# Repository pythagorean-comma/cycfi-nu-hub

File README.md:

# Cycfi Nu Hub

A 6-channel hub board for wiring six individual **Cycfi Nu v2 capsules** into a v2.6
**Cycfi Internal Breakout** on channels 1–6.

Built against Cycfi's published Eagle sources at
<https://github.com/cycfi/nu>

50 × 35 mm on the **Internal Breakout's own outline and M2 hole pattern**, two
layers, and **no components** — thirteen connectors, a grounding pad and some
copper. The capsules already decouple themselves, so there is nothing left for
this board to do but join things up correctly.

The outline is measured from Cycfi's Eagle files, which are **v2.5**; no
dimension has ever been published for the v2.6 this hub is wired for. That
costs nothing electrically and is an open assumption mechanically — see
[`docs/DESIGN.md`](docs/DESIGN.md).

## Everything is generated

`design.py` is the single source of truth for the circuit. `gen_sch.py` draws
the schematic from it, `gen_pcb.py` places and routes the board from it, and
`verify.py` reads KiCad's own netlist back and compares it net by net.

```bash
./build.sh
```

That regenerates schematic *and* board, runs ERC, checks both against
`design.py`, runs DRC, and writes `fab/cycfi-nu-hub-pcbway.zip`, but **only
when DRC is clean**, so a board with known faults cannot reach a fab by
accident.

## Two boards

There is a second variant that **deletes the Internal Breakout entirely** and
drives the instrument's 19-pin output jack itself — 35 × 24.5 mm, half the
area, one polyfuse and one capacitor:

```bash
./build.sh direct
```

The capsule end of both boards is identical; only what the six channels arrive
at differs. The generators are shared and `design.VARIANT` picks between them.

**Order the default one.** The direct variant assumes the v2.6 breakout
presents its jack on the same two 2×5 headers v2.5 does, and nobody has
checked that against hardware. [`docs/DESIGN.md`](docs/DESIGN.md) has the
evidence, the two components' justification, and the one safety property that
regresses.

> **Anything changed in the KiCad GUI is destroyed by the next build.** Use the
> editor to inspect, measure and try things out; changes that should survive
> belong in the generator.

`design.py` also holds the two pin maps transcribed from Cycfi's schematics
and asserts the board against them at import, so a hub wired to the wrong
channels fails to load rather than fails on the bench.

## Requirements

**KiCad 10.x.** Install with `brew install --cask kicad`, or from
<https://www.kicad.org/download/>. The file formats written are version
specific: KiCad 9 will not open the generated schematic.

**No Python packages.** There is no virtual environment and no
`requirements.txt`, because there is nothing to install: the generators are
pure standard library. The one exception is `pcbnew`, which ships inside KiCad,
so `build.sh` runs `gen_pcb.py` under KiCad's own bundled interpreter and
everything else under `python3`. Set `PYTHON` to override which one.

`kicad.py` finds the installation. It checks `$KICAD_APP`, then
`/Applications/KiCad/KiCad.app`, then `~/Applications/KiCad/KiCad.app`, then
`kicad-cli` on `PATH`. If yours lives somewhere else:

```bash
export KICAD_APP=/path/to/KiCad.app
```

Run `python3 kicad.py` to see what it found.

## Where to read next

| | |
| --- | --- |
| [`docs/DESIGN.md`](docs/DESIGN.md) | What the board does and why, what must not be got wrong when wiring it, how it came out, and what is still open. **Start here.** |
| [`docs/CABLES.md`](docs/CABLES.md) | How to make the thirteen cables: parts, suppliers, position-by-position tables, and the continuity checks to run before anything is powered. |
| [`fab/ORDER.md`](fab/ORDER.md) | How to order it, including the four requirements that are invisible in the gerbers, and what to buy alongside it. It lives beside the gerbers rather than in `docs/` because `build.sh` copies it into the fabrication zip and `verify.py` checks the board against its figures. |
| [`docs/cycfi-sources.md`](docs/cycfi-sources.md) | What Cycfi's own files say, at a recorded commit, and how to re-extract it. Records, not specifications — where they and `docs/DESIGN.md` differ, `docs/DESIGN.md` is right. |

## Status

Generated, checked and clean: ERC 0, DRC 0 — **warnings included, not just
errors** — and the schematic matches `design.py` across 8 nets and 39 pin
connections. A fabrication package is written.

**Nothing has been made yet.** No board has been fabricated, no cable crimped
and nothing measured, so every claim in this repository comes from Cycfi's
sources and from the generators — not from a bench.

Three things to settle before ordering, all in the last section of
[`docs/DESIGN.md`](docs/DESIGN.md): Cycfi publish sources for breakout **v2.5** and this
targets **v2.6**, which is three continuity readings on J3 to confirm; the
breakout's `PWR SELECT` jumper decides what voltage six capsules will see; and
the outline copied here is **v2.5's**, because no dimension for v2.6 has ever
been published. Measuring a v2.6 board — width, height, hole diameter, hole
centres — is what closes the last one, and `design.MOUNTING_PATTERN` is the
single block that would change.

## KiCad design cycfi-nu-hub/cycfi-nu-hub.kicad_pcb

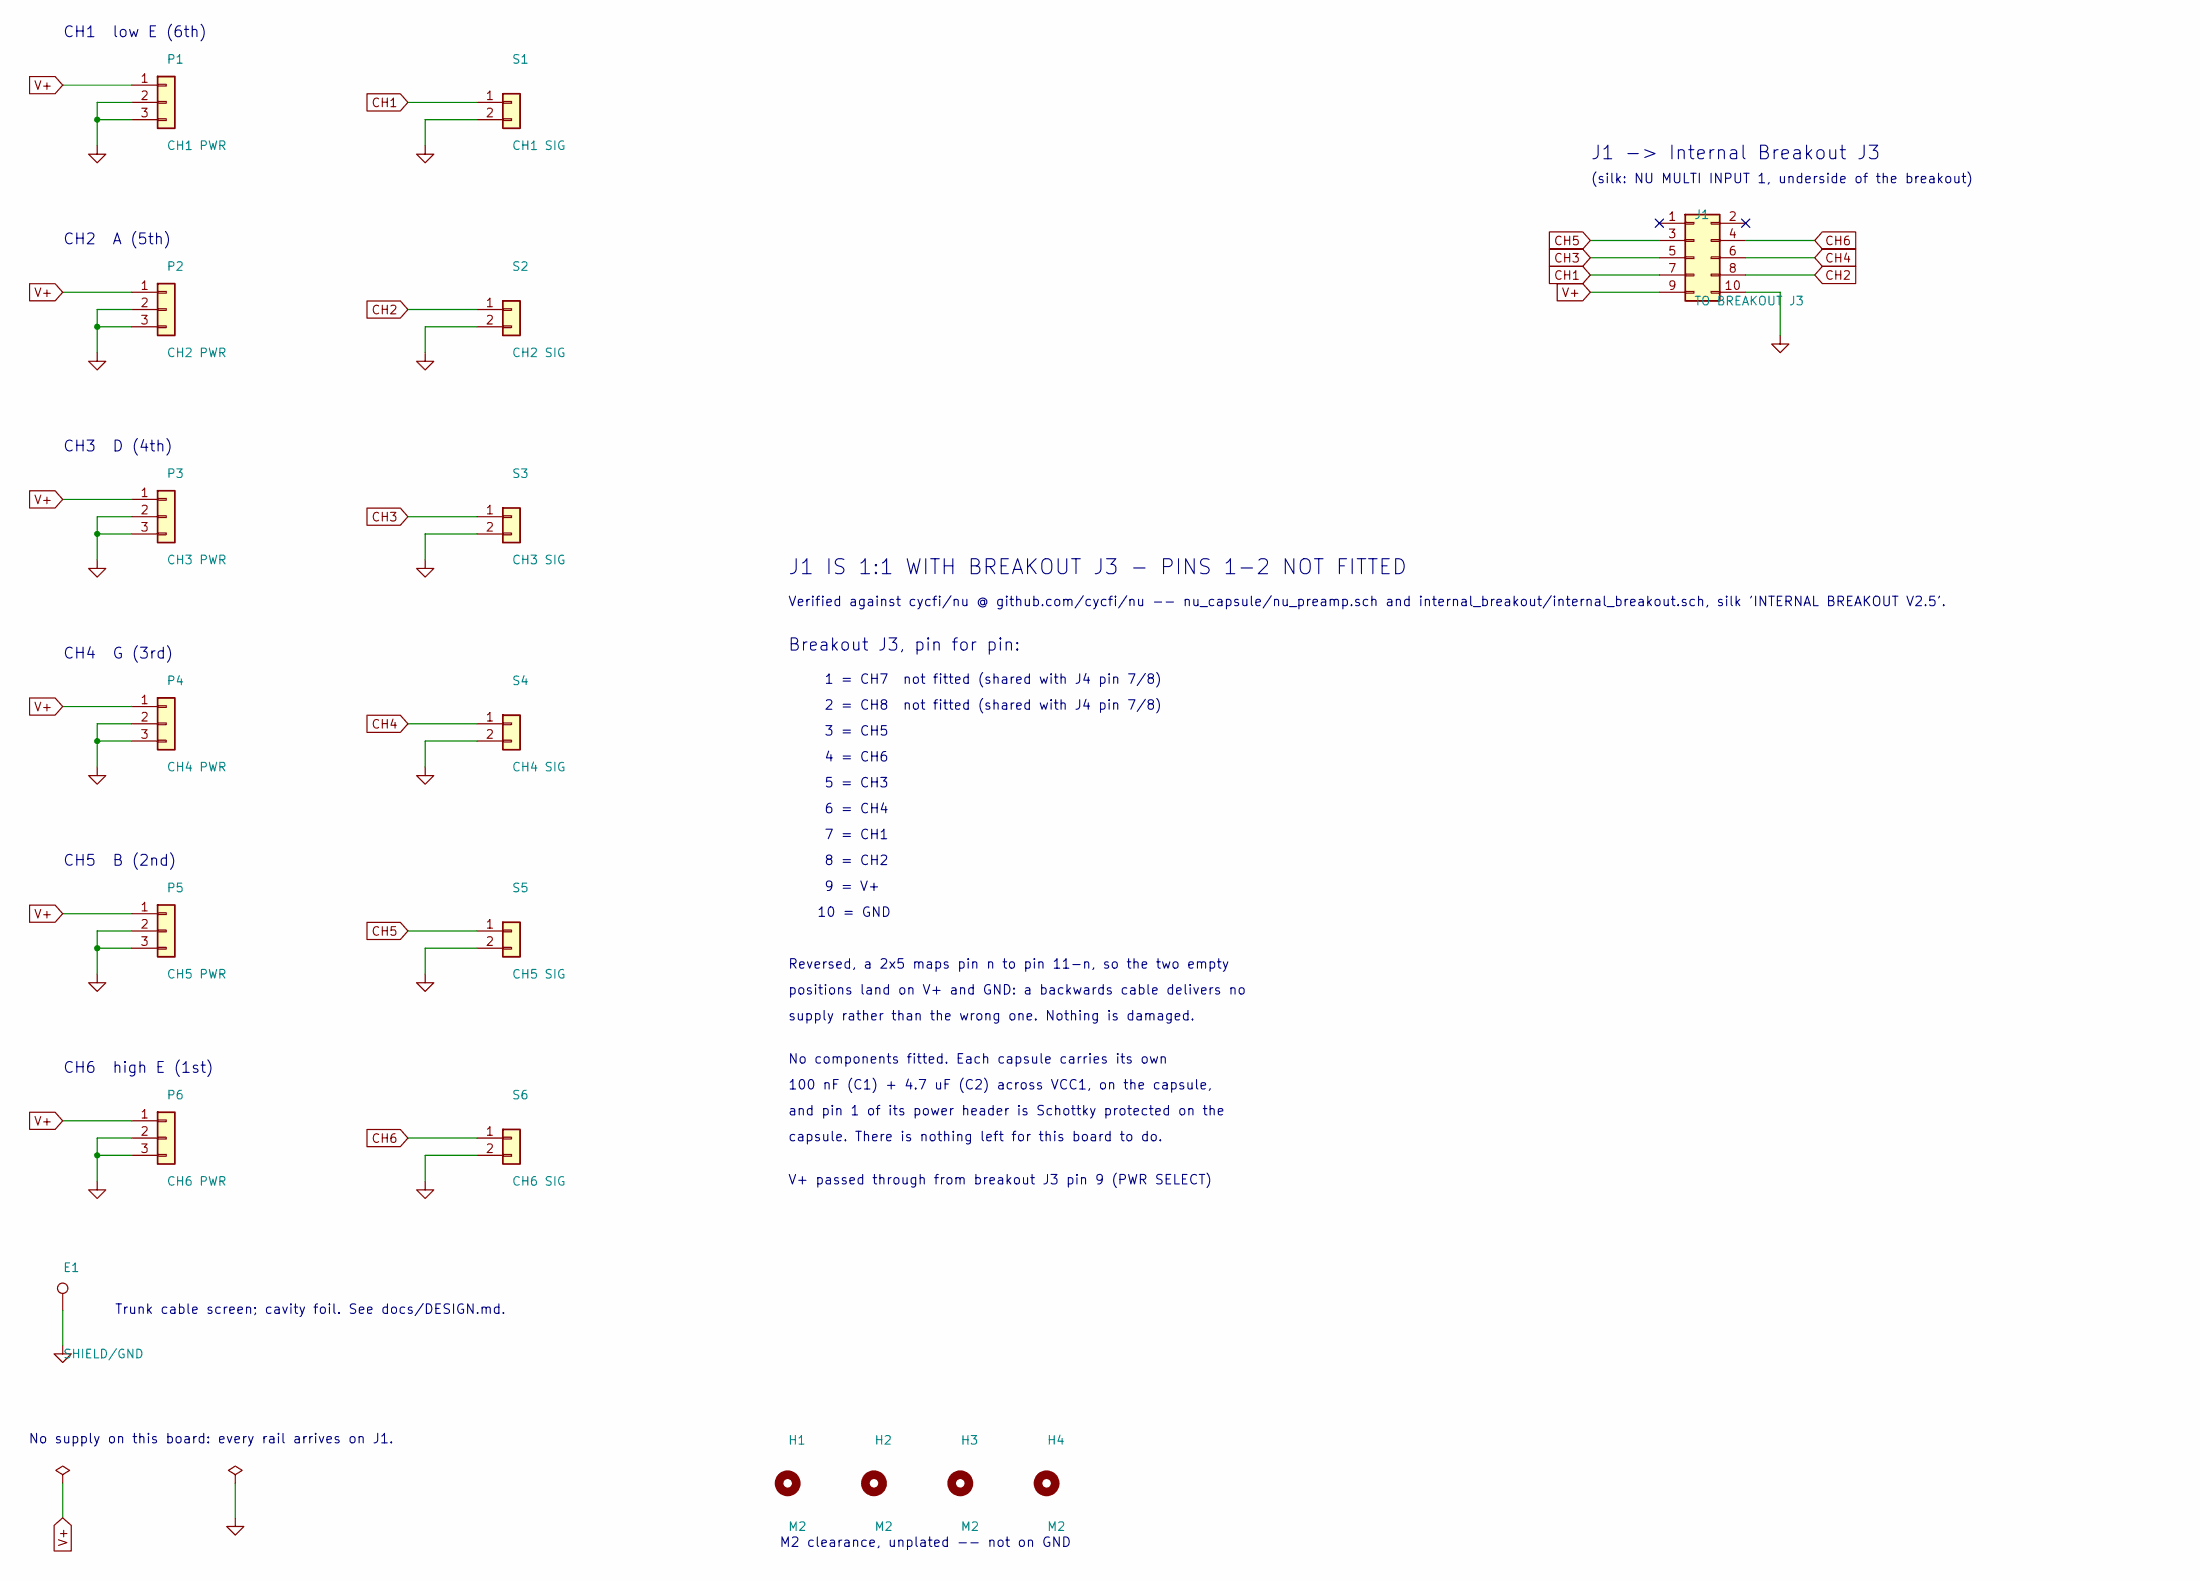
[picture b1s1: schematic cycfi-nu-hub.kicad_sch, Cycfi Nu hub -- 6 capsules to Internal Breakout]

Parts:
E1: SHIELD/GND; TestPoint_THTPad_2.0x2.0mm_Drill1.0mm
H1, H2, H3, H4: M2; MountingHole_2.2mm_M2
J1: TO BREAKOUT J3; PinHeader_2x05_P2.00mm_Vertical
P1: CH1 PWR; PinHeader_1x03_P2.00mm_Vertical
P2: CH2 PWR; PinHeader_1x03_P2.00mm_Vertical
P3: CH3 PWR; PinHeader_1x03_P2.00mm_Vertical
P4: CH4 PWR; PinHeader_1x03_P2.00mm_Vertical
P5: CH5 PWR; PinHeader_1x03_P2.00mm_Vertical
P6: CH6 PWR; PinHeader_1x03_P2.00mm_Vertical
S1: CH1 SIG; PinHeader_1x02_P2.00mm_Vertical
S2: CH2 SIG; PinHeader_1x02_P2.00mm_Vertical
S3: CH3 SIG; PinHeader_1x02_P2.00mm_Vertical
S4: CH4 SIG; PinHeader_1x02_P2.00mm_Vertical
S5: CH5 SIG; PinHeader_1x02_P2.00mm_Vertical
S6: CH6 SIG; PinHeader_1x02_P2.00mm_Vertical

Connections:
CH1: J1.7, S1.1
CH2: J1.8, S2.1
CH3: J1.5, S3.1
CH4: J1.6, S4.1
CH5: J1.3, S5.1
CH6: J1.4, S6.1
GND: E1.1, J1.10, P1.2, P1.3, P2.2, P2.3, P3.2, P3.3, P4.2, P4.3, P5.2, P5.3, P6.2, P6.3, S1.2, S2.2, S3.2, S4.2, S5.2, S6.2
V+: J1.9, P1.1, P2.1, P3.1, P4.1, P5.1, P6.1

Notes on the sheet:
CH1 low E (6th)
CH2 A (5th)
CH3 D (4th)
CH4 G (3rd)
CH5 B (2nd)
CH6 high E (1st)
J1 -> Internal Breakout J3
(silk: NU MULTI INPUT 1, underside of the breakout)
Trunk cable screen; cavity foil. See docs/DESIGN.md.
M2 clearance, unplated -- not on GND
No supply on this board: every rail arrives on J1.
J1 IS 1:1 WITH BREAKOUT J3 - PINS 1-2 NOT FITTED
Verified against cycfi/nu @ github.com/cycfi/nu -- nu_capsule/nu_preamp.sch and internal_breakout/internal_breakout.sch, silk 'INTERNAL BREAKOUT V2.5'.
Breakout J3, pin for pin:
1 = CH7 not fitted (shared with J4 pin 7/8)
2 = CH8 not fitted (shared with J4 pin 7/8)
3 = CH5
4 = CH6
5 = CH3
6 = CH4
7 = CH1
8 = CH2
9 = V+
10 = GND
Reversed, a 2x5 maps pin n to pin 11-n, so the two empty
positions land on V+ and GND: a backwards cable delivers no
supply rather than the wrong one. Nothing is damaged.
No components fitted. Each capsule carries its own
100 nF (C1) + 4.7 uF (C2) across VCC1, on the capsule,
and pin 1 of its power header is Schottky protected on the
capsule. There is nothing left for this board to do.
V+ passed through from breakout J3 pin 9 (PWR SELECT)

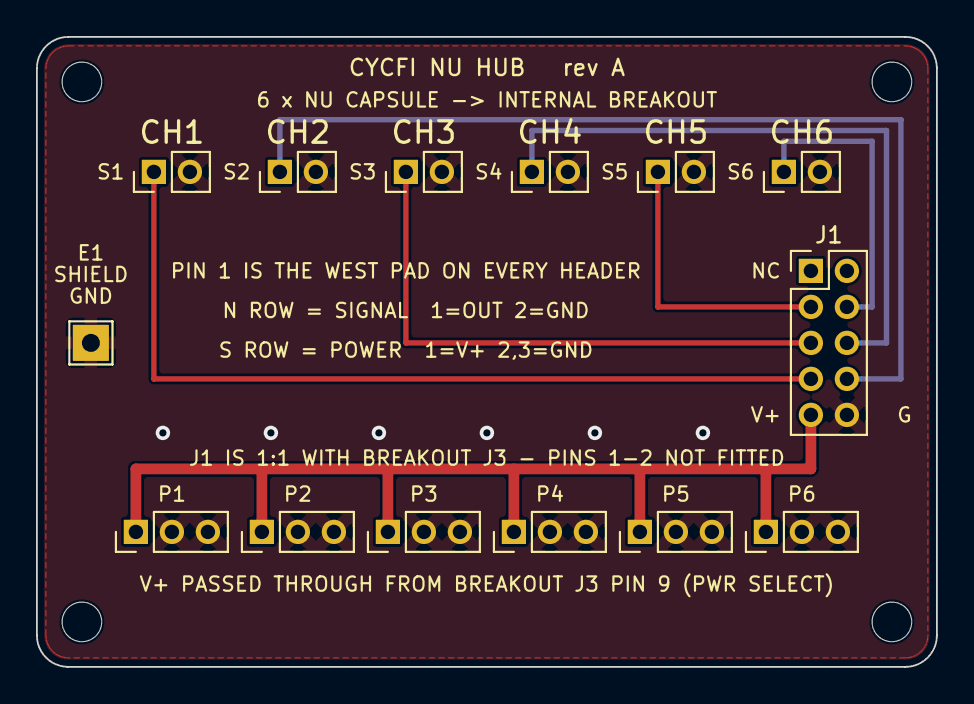
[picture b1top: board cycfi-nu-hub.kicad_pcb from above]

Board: 2 copper layers, 50.0 x 35.0 mm, 18 parts (0 on the bottom side), 8 nets.

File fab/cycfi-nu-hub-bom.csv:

"Reference","Value","Footprint","QUANTITY","Description"
"E1","SHIELD/GND","TestPoint:TestPoint_THTPad_2.0x2.0mm_Drill1.0mm","1","Solder pad to GND: trunk cable screen, cavity foil, optionally bridge earth"
"H1-H4","M2","MountingHole:MountingHole_2.2mm_M2","4","M2 clearance hole, unplated"
"J1","TO BREAKOUT J3","Connector_PinHeader_2.00mm:PinHeader_2x05_P2.00mm_Vertical","1","2x5 2.00mm to Internal Breakout J3 (NU MULTI INPUT 1); pins 1-2 not fitted"
"P1","CH1 PWR","Connector_PinHeader_2.00mm:PinHeader_1x03_P2.00mm_Vertical","1","Capsule 1, low E (6th) -- power, to capsule H2: 1=V+, 2=GND, 3=GND"
"P2","CH2 PWR","Connector_PinHeader_2.00mm:PinHeader_1x03_P2.00mm_Vertical","1","Capsule 2, A (5th) -- power, to capsule H2: 1=V+, 2=GND, 3=GND"
"P3","CH3 PWR","Connector_PinHeader_2.00mm:PinHeader_1x03_P2.00mm_Vertical","1","Capsule 3, D (4th) -- power, to capsule H2: 1=V+, 2=GND, 3=GND"
"P4","CH4 PWR","Connector_PinHeader_2.00mm:PinHeader_1x03_P2.00mm_Vertical","1","Capsule 4, G (3rd) -- power, to capsule H2: 1=V+, 2=GND, 3=GND"
"P5","CH5 PWR","Connector_PinHeader_2.00mm:PinHeader_1x03_P2.00mm_Vertical","1","Capsule 5, B (2nd) -- power, to capsule H2: 1=V+, 2=GND, 3=GND"
"P6","CH6 PWR","Connector_PinHeader_2.00mm:PinHeader_1x03_P2.00mm_Vertical","1","Capsule 6, high E (1st) -- power, to capsule H2: 1=V+, 2=GND, 3=GND"
"S1","CH1 SIG","Connector_PinHeader_2.00mm:PinHeader_1x02_P2.00mm_Vertical","1","Capsule 1, low E (6th) -- signal, to capsule H1: 1=OUT, 2=GND"
"S2","CH2 SIG","Connector_PinHeader_2.00mm:PinHeader_1x02_P2.00mm_Vertical","1","Capsule 2, A (5th) -- signal, to capsule H1: 1=OUT, 2=GND"
"S3","CH3 SIG","Connector_PinHeader_2.00mm:PinHeader_1x02_P2.00mm_Vertical","1","Capsule 3, D (4th) -- signal, to capsule H1: 1=OUT, 2=GND"
"S4","CH4 SIG","Connector_PinHeader_2.00mm:PinHeader_1x02_P2.00mm_Vertical","1","Capsule 4, G (3rd) -- signal, to capsule H1: 1=OUT, 2=GND"
"S5","CH5 SIG","Connector_PinHeader_2.00mm:PinHeader_1x02_P2.00mm_Vertical","1","Capsule 5, B (2nd) -- signal, to capsule H1: 1=OUT, 2=GND"
"S6","CH6 SIG","Connector_PinHeader_2.00mm:PinHeader_1x02_P2.00mm_Vertical","1","Capsule 6, high E (1st) -- signal, to capsule H1: 1=OUT, 2=GND"

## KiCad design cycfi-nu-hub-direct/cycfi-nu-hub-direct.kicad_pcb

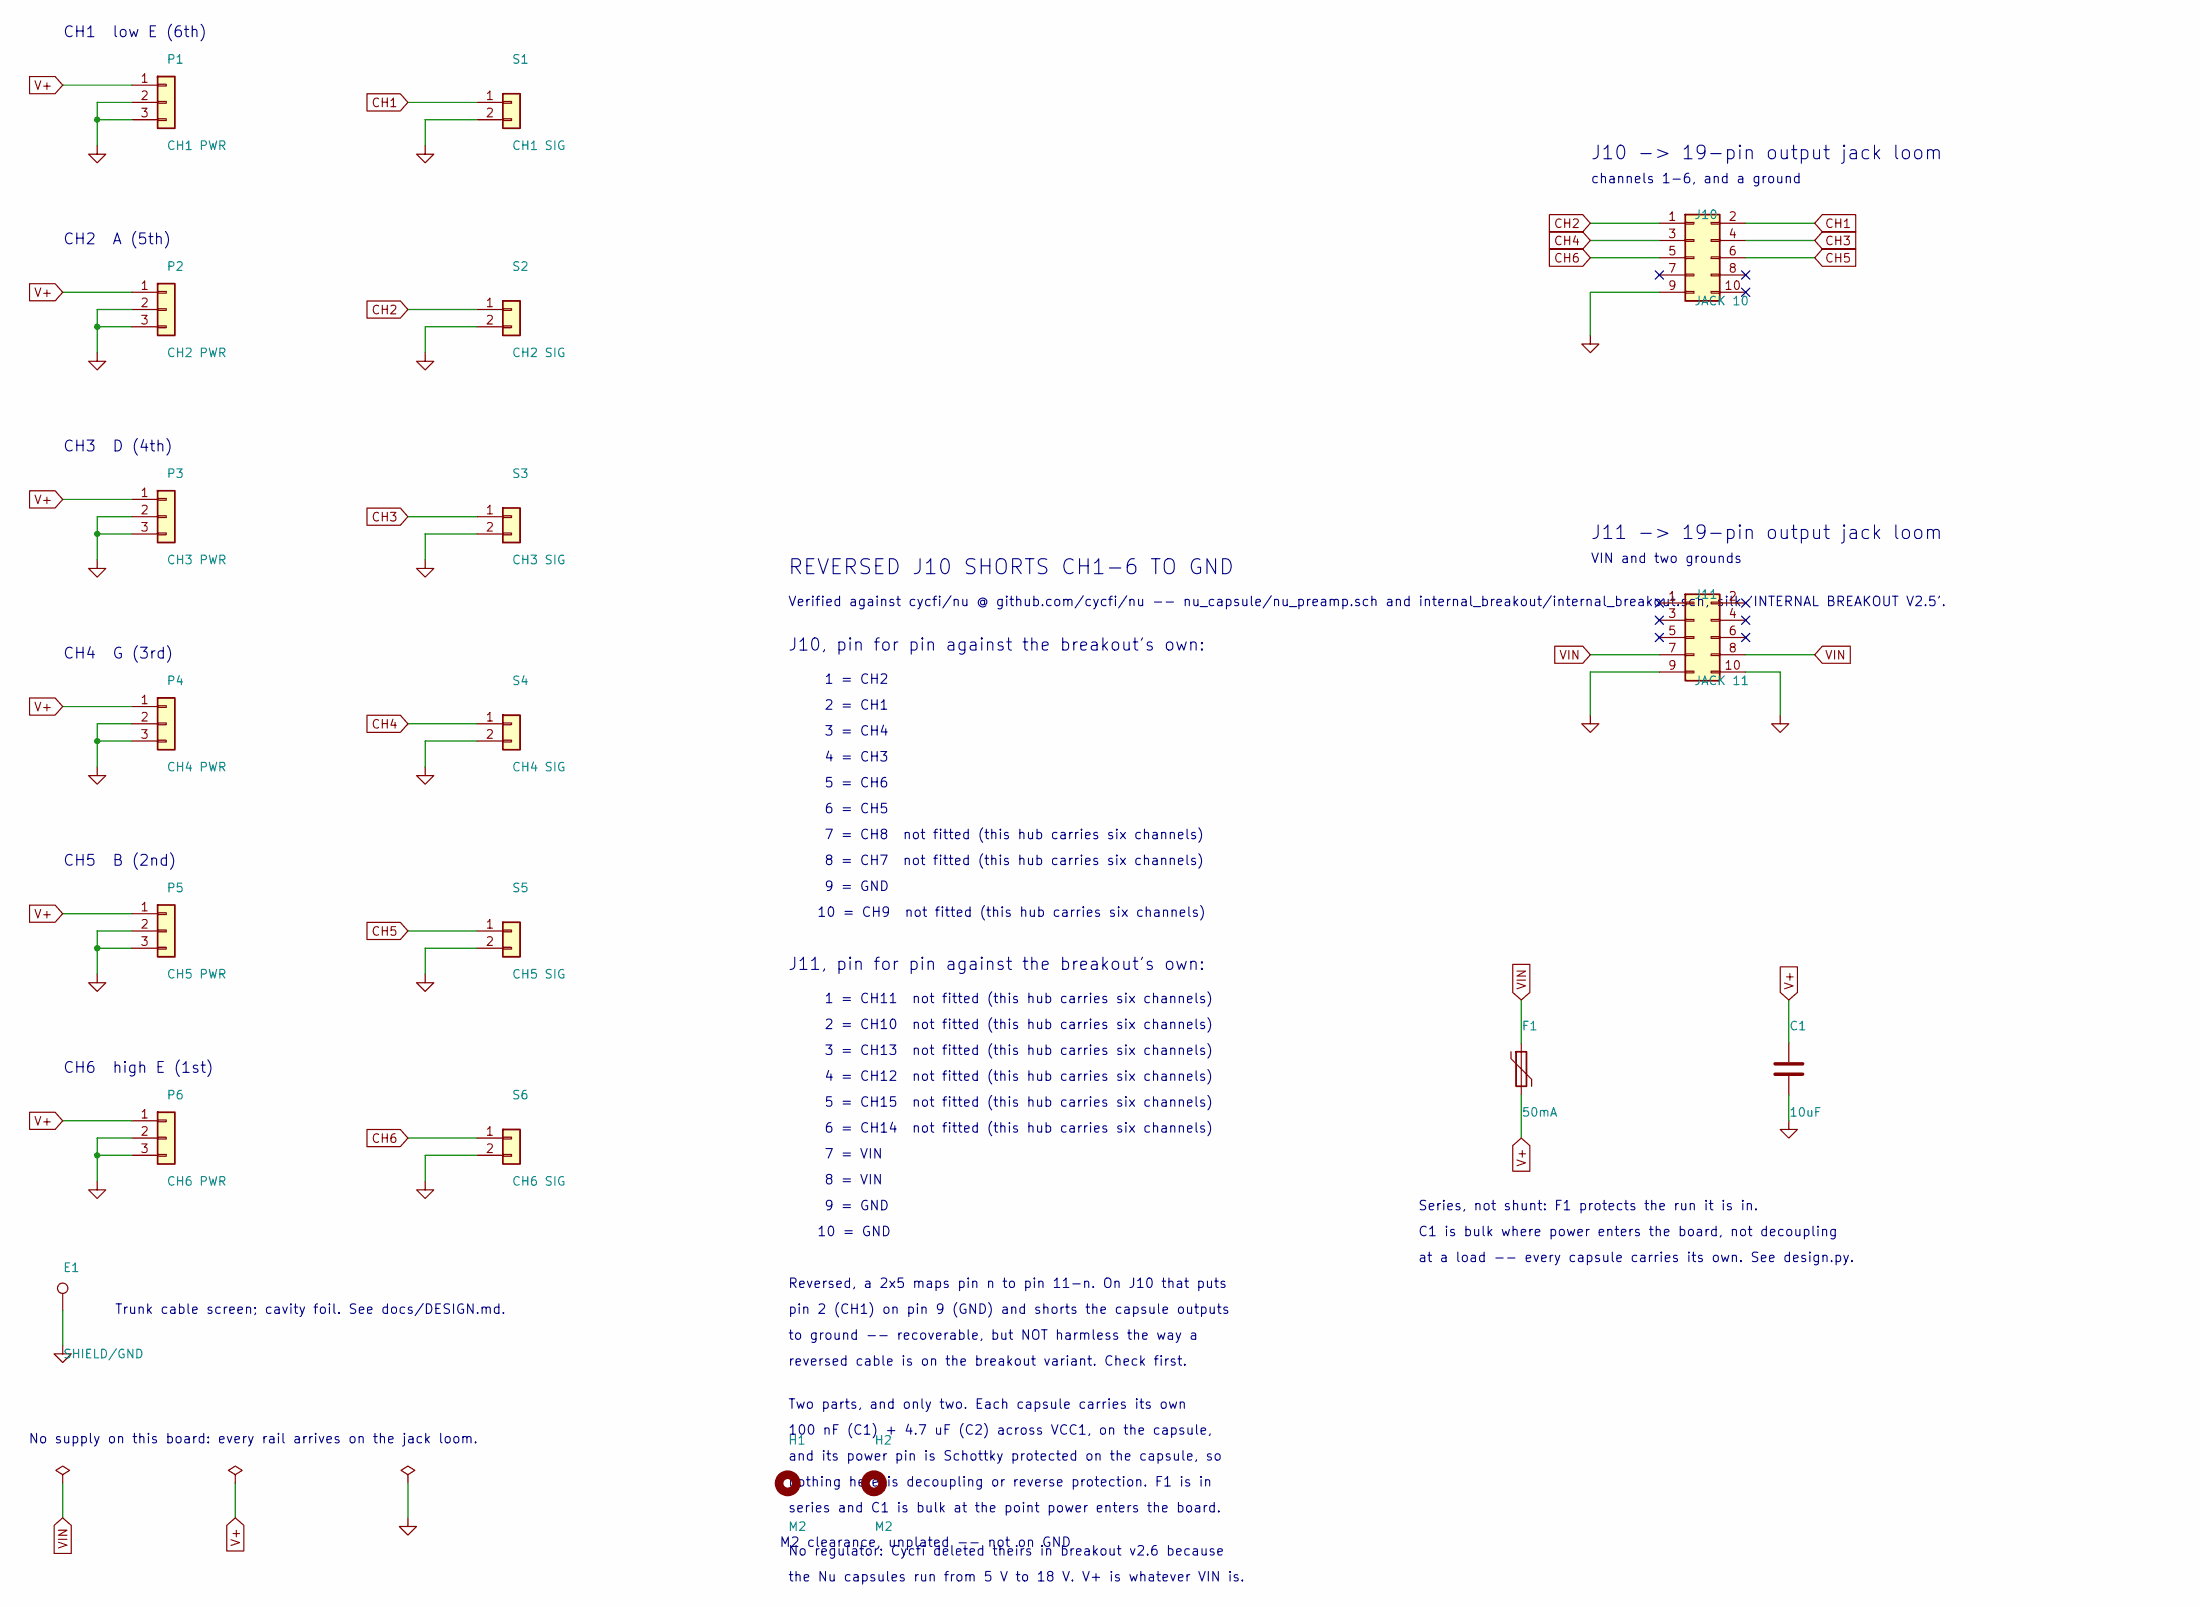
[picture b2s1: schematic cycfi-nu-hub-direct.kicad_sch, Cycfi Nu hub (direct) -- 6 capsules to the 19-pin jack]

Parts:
C1: 10uF; C_0805_2012Metric
E1: SHIELD/GND; TestPoint_THTPad_2.0x2.0mm_Drill1.0mm
F1: 50mA; Fuse_0805_2012Metric
H1, H2: M2; MountingHole_2.2mm_M2
J10: JACK 10; PinHeader_2x05_P2.00mm_Vertical
J11: JACK 11; PinHeader_2x05_P2.00mm_Vertical
P1: CH1 PWR; PinHeader_1x03_P2.00mm_Vertical
P2: CH2 PWR; PinHeader_1x03_P2.00mm_Vertical
P3: CH3 PWR; PinHeader_1x03_P2.00mm_Vertical
P4: CH4 PWR; PinHeader_1x03_P2.00mm_Vertical
P5: CH5 PWR; PinHeader_1x03_P2.00mm_Vertical
P6: CH6 PWR; PinHeader_1x03_P2.00mm_Vertical
S1: CH1 SIG; PinHeader_1x02_P2.00mm_Vertical
S2: CH2 SIG; PinHeader_1x02_P2.00mm_Vertical
S3: CH3 SIG; PinHeader_1x02_P2.00mm_Vertical
S4: CH4 SIG; PinHeader_1x02_P2.00mm_Vertical
S5: CH5 SIG; PinHeader_1x02_P2.00mm_Vertical
S6: CH6 SIG; PinHeader_1x02_P2.00mm_Vertical

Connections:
CH1: J10.2, S1.1
CH2: J10.1, S2.1
CH3: J10.4, S3.1
CH4: J10.3, S4.1
CH5: J10.6, S5.1
CH6: J10.5, S6.1
GND: C1.2, E1.1, J10.9, J11.9, J11.10, P1.2, P1.3, P2.2, P2.3, P3.2, P3.3, P4.2, P4.3, P5.2, P5.3, P6.2, P6.3, S1.2, S2.2, S3.2, S4.2, S5.2, S6.2
V+: C1.1, F1.2, P1.1, P2.1, P3.1, P4.1, P5.1, P6.1
VIN: F1.1, J11.7, J11.8

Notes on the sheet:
CH1 low E (6th)
CH2 A (5th)
CH3 D (4th)
CH4 G (3rd)
CH5 B (2nd)
CH6 high E (1st)
J10 -> 19-pin output jack loom
channels 1-6, and a ground
J11 -> 19-pin output jack loom
VIN and two grounds
Series, not shunt: F1 protects the run it is in.
C1 is bulk where power enters the board, not decoupling
at a load -- every capsule carries its own. See design.py.
Trunk cable screen; cavity foil. See docs/DESIGN.md.
M2 clearance, unplated -- not on GND
No supply on this board: every rail arrives on the jack loom.
REVERSED J10 SHORTS CH1-6 TO GND
Verified against cycfi/nu @ github.com/cycfi/nu -- nu_capsule/nu_preamp.sch and internal_breakout/internal_breakout.sch, silk 'INTERNAL BREAKOUT V2.5'.
J10, pin for pin against the breakout's own:
1 = CH2
2 = CH1
3 = CH4
4 = CH3
5 = CH6
6 = CH5
7 = CH8 not fitted (this hub carries six channels)
8 = CH7 not fitted (this hub carries six channels)
9 = GND
10 = CH9 not fitted (this hub carries six channels)
J11, pin for pin against the breakout's own:
1 = CH11 not fitted (this hub carries six channels)
2 = CH10 not fitted (this hub carries six channels)
3 = CH13 not fitted (this hub carries six channels)
4 = CH12 not fitted (this hub carries six channels)
5 = CH15 not fitted (this hub carries six channels)
6 = CH14 not fitted (this hub carries six channels)
7 = VIN
8 = VIN
10 = GND
Reversed, a 2x5 maps pin n to pin 11-n. On J10 that puts

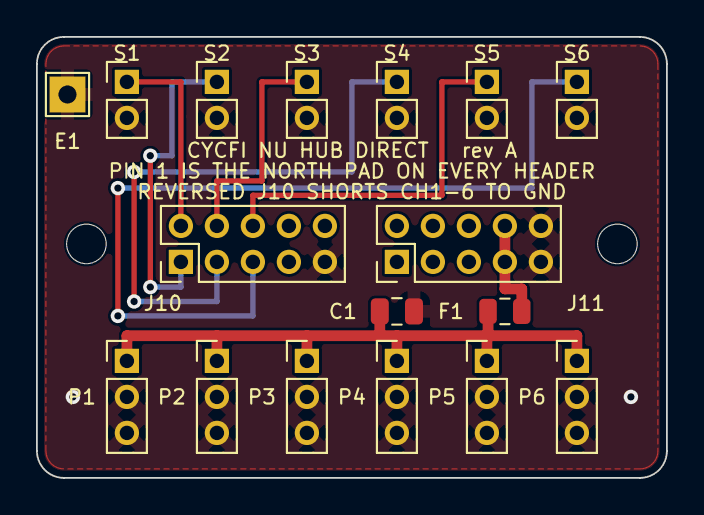
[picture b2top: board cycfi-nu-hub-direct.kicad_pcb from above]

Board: 2 copper layers, 35.0 x 24.5 mm, 19 parts (0 on the bottom side), 9 nets.

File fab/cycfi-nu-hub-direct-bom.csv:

"Reference","Value","Footprint","QUANTITY","Description"
"C1","10uF","Capacitor_SMD:C_0805_2012Metric","1","Bulk across V+ at the point power enters the board; not decoupling -- see NO_COMPONENTS"
"E1","SHIELD/GND","TestPoint:TestPoint_THTPad_2.0x2.0mm_Drill1.0mm","1","Solder pad to GND: trunk cable screen, cavity foil, optionally bridge earth"
"F1","50mA","Fuse:Fuse_0805_2012Metric","1","Polyfuse, 50 mA hold -- series protection for the six capsule supplies"
"H1,H2","M2","MountingHole:MountingHole_2.2mm_M2","2","M2 clearance hole, unplated"
"J10","JACK 10","Connector_PinHeader_2.00mm:PinHeader_2x05_P2.00mm_Vertical","1","2x5 2.00mm to the 19-pin output jack loom -- channels 1-6 and a ground; wired one-to-one with the breakout's J10"
"J11","JACK 11","Connector_PinHeader_2.00mm:PinHeader_2x05_P2.00mm_Vertical","1","2x5 2.00mm to the 19-pin output jack loom -- VIN and two grounds; wired one-to-one with the breakout's J11"
"P1","CH1 PWR","Connector_PinHeader_2.00mm:PinHeader_1x03_P2.00mm_Vertical","1","Capsule 1, low E (6th) -- power, to capsule H2: 1=V+, 2=GND, 3=GND"
"P2","CH2 PWR","Connector_PinHeader_2.00mm:PinHeader_1x03_P2.00mm_Vertical","1","Capsule 2, A (5th) -- power, to capsule H2: 1=V+, 2=GND, 3=GND"
"P3","CH3 PWR","Connector_PinHeader_2.00mm:PinHeader_1x03_P2.00mm_Vertical","1","Capsule 3, D (4th) -- power, to capsule H2: 1=V+, 2=GND, 3=GND"
"P4","CH4 PWR","Connector_PinHeader_2.00mm:PinHeader_1x03_P2.00mm_Vertical","1","Capsule 4, G (3rd) -- power, to capsule H2: 1=V+, 2=GND, 3=GND"
"P5","CH5 PWR","Connector_PinHeader_2.00mm:PinHeader_1x03_P2.00mm_Vertical","1","Capsule 5, B (2nd) -- power, to capsule H2: 1=V+, 2=GND, 3=GND"
"P6","CH6 PWR","Connector_PinHeader_2.00mm:PinHeader_1x03_P2.00mm_Vertical","1","Capsule 6, high E (1st) -- power, to capsule H2: 1=V+, 2=GND, 3=GND"
"S1","CH1 SIG","Connector_PinHeader_2.00mm:PinHeader_1x02_P2.00mm_Vertical","1","Capsule 1, low E (6th) -- signal, to capsule H1: 1=OUT, 2=GND"
"S2","CH2 SIG","Connector_PinHeader_2.00mm:PinHeader_1x02_P2.00mm_Vertical","1","Capsule 2, A (5th) -- signal, to capsule H1: 1=OUT, 2=GND"
"S3","CH3 SIG","Connector_PinHeader_2.00mm:PinHeader_1x02_P2.00mm_Vertical","1","Capsule 3, D (4th) -- signal, to capsule H1: 1=OUT, 2=GND"
"S4","CH4 SIG","Connector_PinHeader_2.00mm:PinHeader_1x02_P2.00mm_Vertical","1","Capsule 4, G (3rd) -- signal, to capsule H1: 1=OUT, 2=GND"
"S5","CH5 SIG","Connector_PinHeader_2.00mm:PinHeader_1x02_P2.00mm_Vertical","1","Capsule 5, B (2nd) -- signal, to capsule H1: 1=OUT, 2=GND"
"S6","CH6 SIG","Connector_PinHeader_2.00mm:PinHeader_1x02_P2.00mm_Vertical","1","Capsule 6, high E (1st) -- signal, to capsule H1: 1=OUT, 2=GND"
